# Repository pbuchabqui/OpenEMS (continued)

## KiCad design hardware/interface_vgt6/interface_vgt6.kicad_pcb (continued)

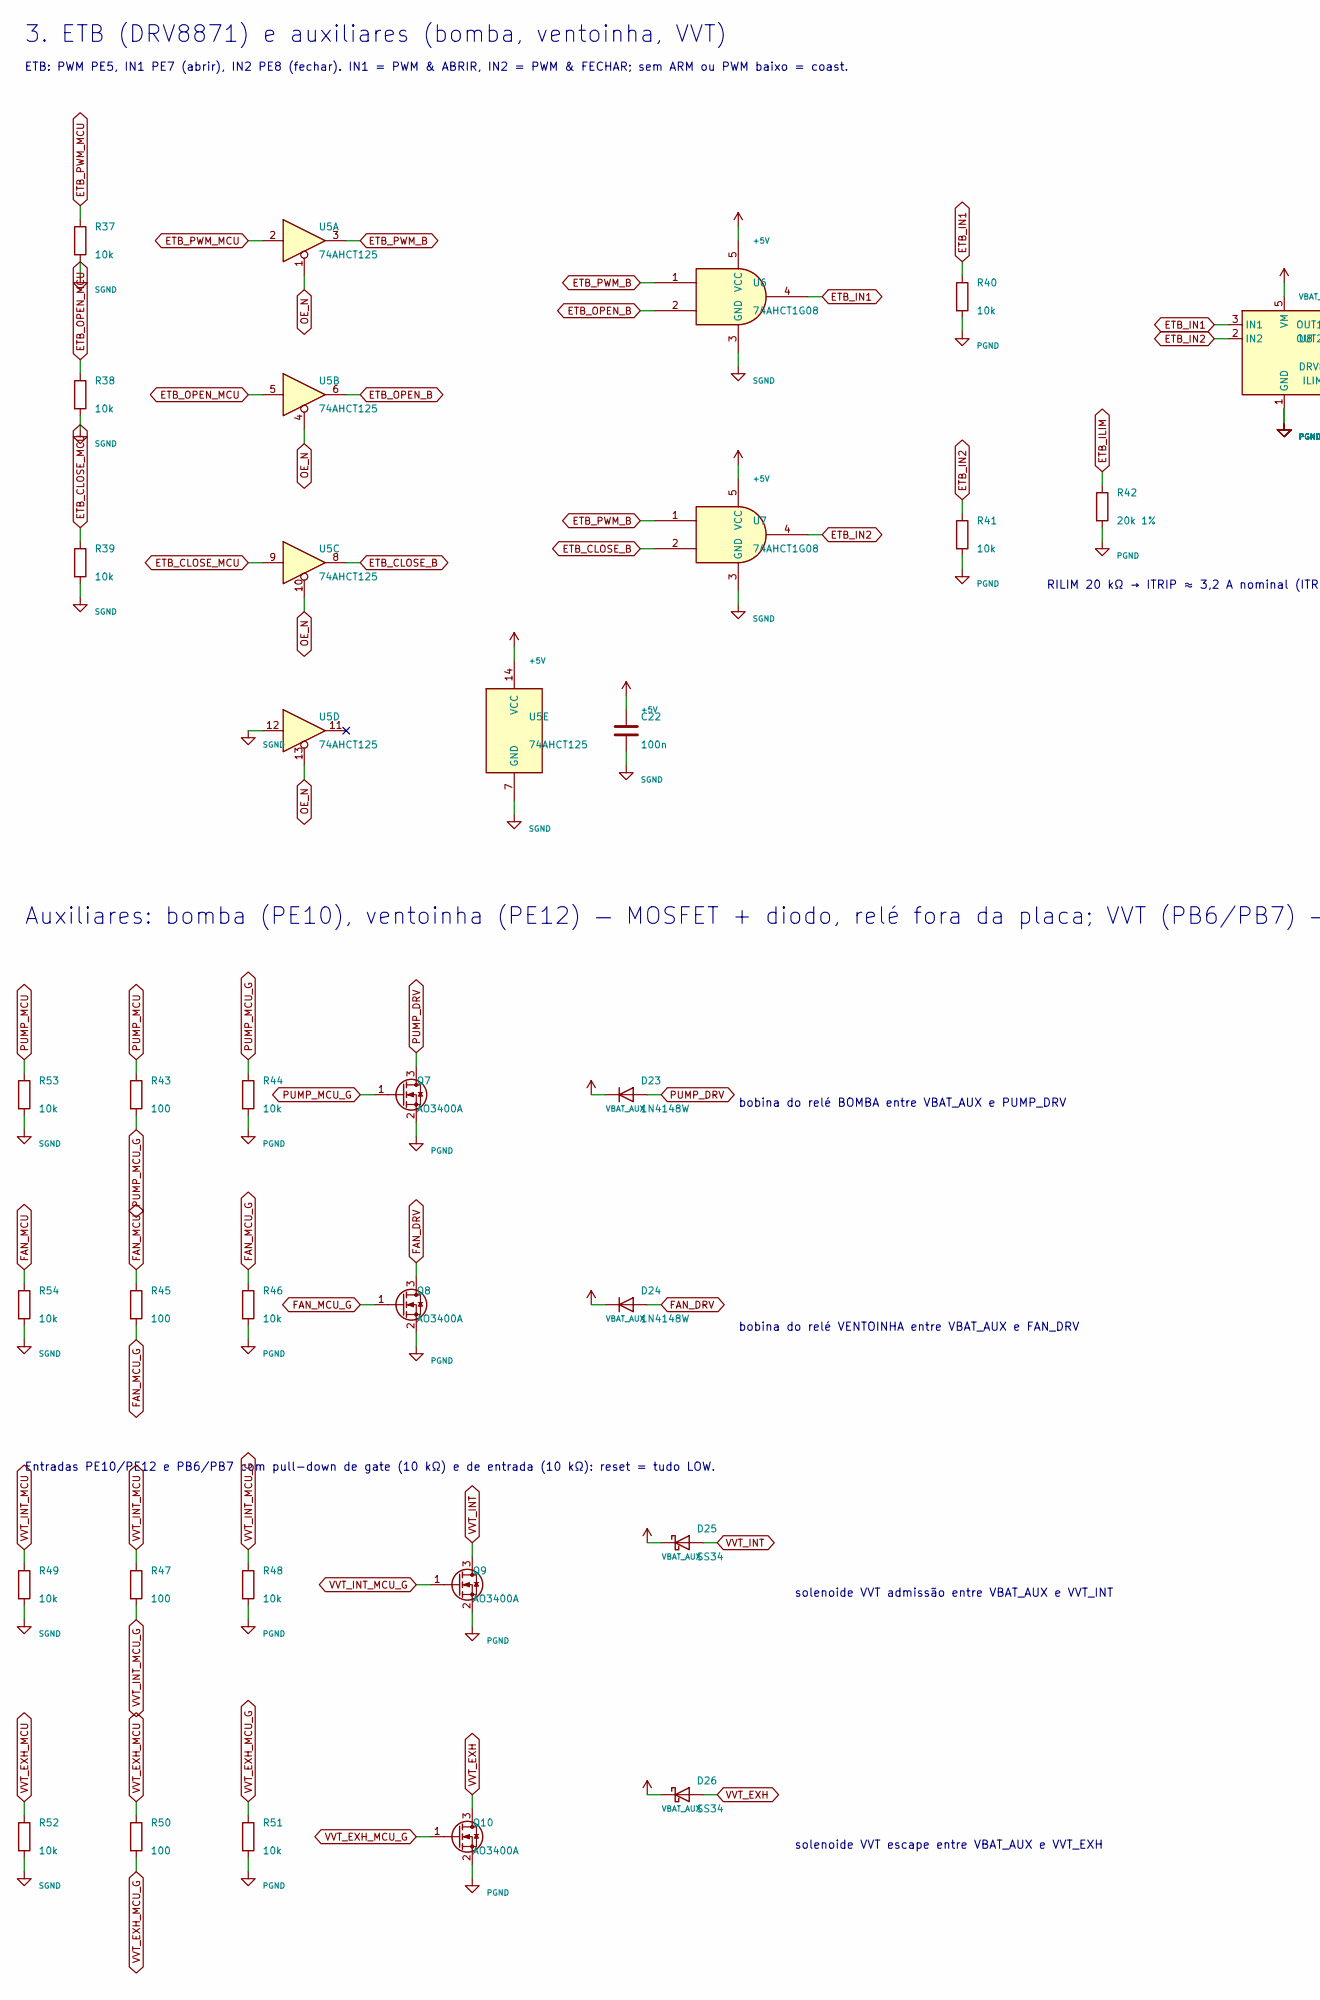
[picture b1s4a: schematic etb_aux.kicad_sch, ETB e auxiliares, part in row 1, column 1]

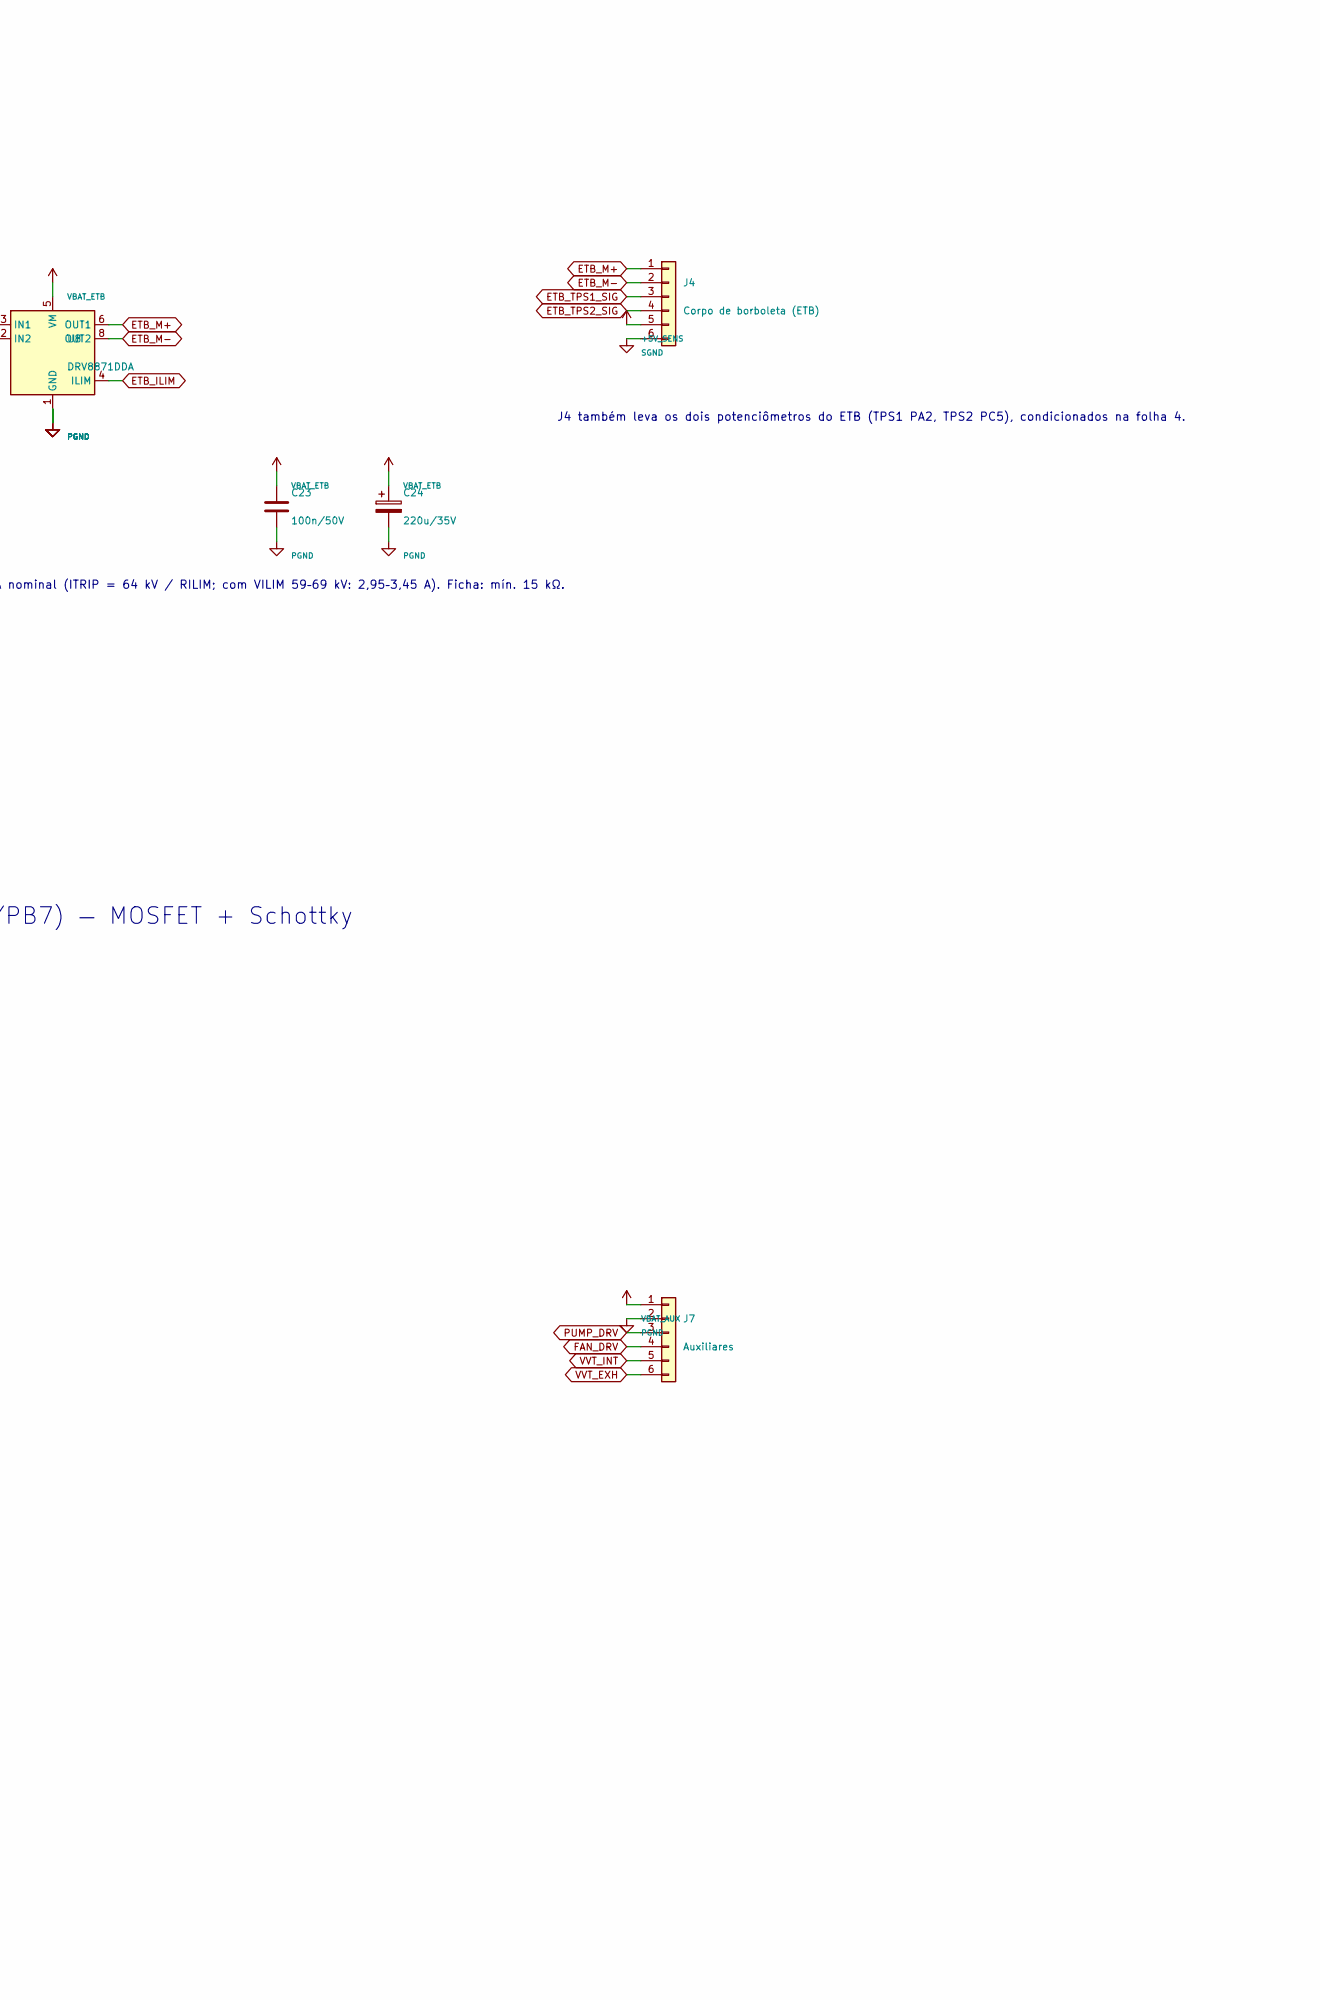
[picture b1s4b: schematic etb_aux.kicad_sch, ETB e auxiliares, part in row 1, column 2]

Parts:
C22: 100n; C_0603_1608Metric
C23: 100n/50V; C_0603_1608Metric
C24: 220u/35V; CP_Elec_8x10
D23, D24: 1N4148W; D_SOD-123
D25, D26: SS34; D_SMA
J4: Corpo de borboleta (ETB); PhoenixContact_MC_1,5_6-G-3.81_1x06_P3.81mm_Horizontal
J7: Auxiliares; PhoenixContact_MSTBA_2,5_6-G-5,08_1x06_P5.08mm_Horizontal
Q7, Q8, Q9, Q10: AO3400A; SOT-23
R37, R38, R39, R40, R41, R44, R46, R48, R49, R51, R52, R53, R54: 10k; R_0603_1608Metric
R42: 20k 1%; R_0603_1608Metric
R43, R45, R47, R50: 100; R_0603_1608Metric
U5: 74AHCT125; TSSOP-14_4.4x5mm_P0.65mm
U6, U7: 74AHCT1G08; SOT-23-5
U8: DRV8871DDA; HSOP-8-1EP_3.9x4.9mm_P1.27mm_EP2.41x3.1mm

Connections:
+5V: C22.1, U5.14 (VCC), U6.5 (VCC), U7.5 (VCC); also elsewhere on the board
+5V_SENS: J4.5; also elsewhere on the board
ETB_CLOSE_B: U5.8, U7.2
ETB_CLOSE_MCU: R39.1, U5.9; also elsewhere on the board
ETB_ILIM: R42.1, U8.4 (ILIM)
ETB_IN1: R40.1, U6.4, U8.3 (IN1)
ETB_IN2: R41.1, U7.4, U8.2 (IN2)
ETB_M+: J4.1, U8.6 (OUT1)
ETB_M-: J4.2, U8.8 (OUT2)
ETB_OPEN_B: U5.6, U6.2
ETB_OPEN_MCU: R38.1, U5.5; also elsewhere on the board
ETB_PWM_B: U5.3, U6.1, U7.1
ETB_PWM_MCU: R37.1, U5.2; also elsewhere on the board
ETB_TPS1_SIG: J4.3; also elsewhere on the board
ETB_TPS2_SIG: J4.4; also elsewhere on the board
FAN_DRV: D24.2 (A), J7.4, Q8.3 (D)
FAN_MCU: R45.1, R54.1; also elsewhere on the board
FAN_MCU_G: Q8.1 (G), R45.2, R46.1
OE_N: U5.1, U5.4, U5.10, U5.13; also elsewhere on the board
PGND: C23.2, C24.2, J7.2, Q7.2 (S), Q8.2 (S), Q9.2 (S), Q10.2 (S), R40.2, R41.2, R42.2, R44.2, R46.2, R48.2, R51.2, U8.1 (GND), U8.7 (GND), U8.9 (GND); also elsewhere on the board
PUMP_DRV: D23.2 (A), J7.3, Q7.3 (D)
PUMP_MCU: R43.1, R53.1; also elsewhere on the board
PUMP_MCU_G: Q7.1 (G), R43.2, R44.1
SGND: C22.2, J4.6, R37.2, R38.2, R39.2, R49.2, R52.2, R53.2, R54.2, U5.7 (GND), U5.12, U6.3 (GND), U7.3 (GND); also elsewhere on the board
VBAT_AUX: D23.1 (K), D24.1 (K), D25.1 (K), D26.1 (K), J7.1; also elsewhere on the board
VBAT_ETB: C23.1, C24.1, U8.5 (VM); also elsewhere on the board
VVT_EXH: D26.2 (A), J7.6, Q10.3 (D)
VVT_EXH_MCU: R50.1, R52.1; also elsewhere on the board
VVT_EXH_MCU_G: Q10.1 (G), R50.2, R51.1
VVT_INT: D25.2 (A), J7.5, Q9.3 (D)
VVT_INT_MCU: R47.1, R49.1; also elsewhere on the board
VVT_INT_MCU_G: Q9.1 (G), R47.2, R48.1

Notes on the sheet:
3. ETB (DRV8871) e auxiliares (bomba, ventoinha, VVT)
ETB: PWM PE5, IN1 PE7 (abrir), IN2 PE8 (fechar). IN1 = PWM & ABRIR, IN2 = PWM & FECHAR; sem ARM ou PWM baixo = coast.
RILIM 20 kΩ → ITRIP ≈ 3,2 A nominal (ITRIP = 64 kV / RILIM; com VILIM 59–69 kV: 2,95–3,45 A). Ficha: mín. 15 kΩ.
J4 também leva os dois potenciômetros do ETB (TPS1 PA2, TPS2 PC5), condicionados na folha 4.
Auxiliares: bomba (PE10), ventoinha (PE12) — MOSFET + diodo, relé fora da placa; VVT (PB6/PB7) — MOSFET + Schottky
bobina do relé BOMBA entre VBAT_AUX e PUMP_DRV
bobina do relé VENTOINHA entre VBAT_AUX e FAN_DRV
solenoide VVT admissão entre VBAT_AUX e VVT_INT
solenoide VVT escape entre VBAT_AUX e VVT_EXH
Entradas PE10/PE12 e PB6/PB7 com pull-down de gate (10 kΩ) e de entrada (10 kΩ): reset = tudo LOW.

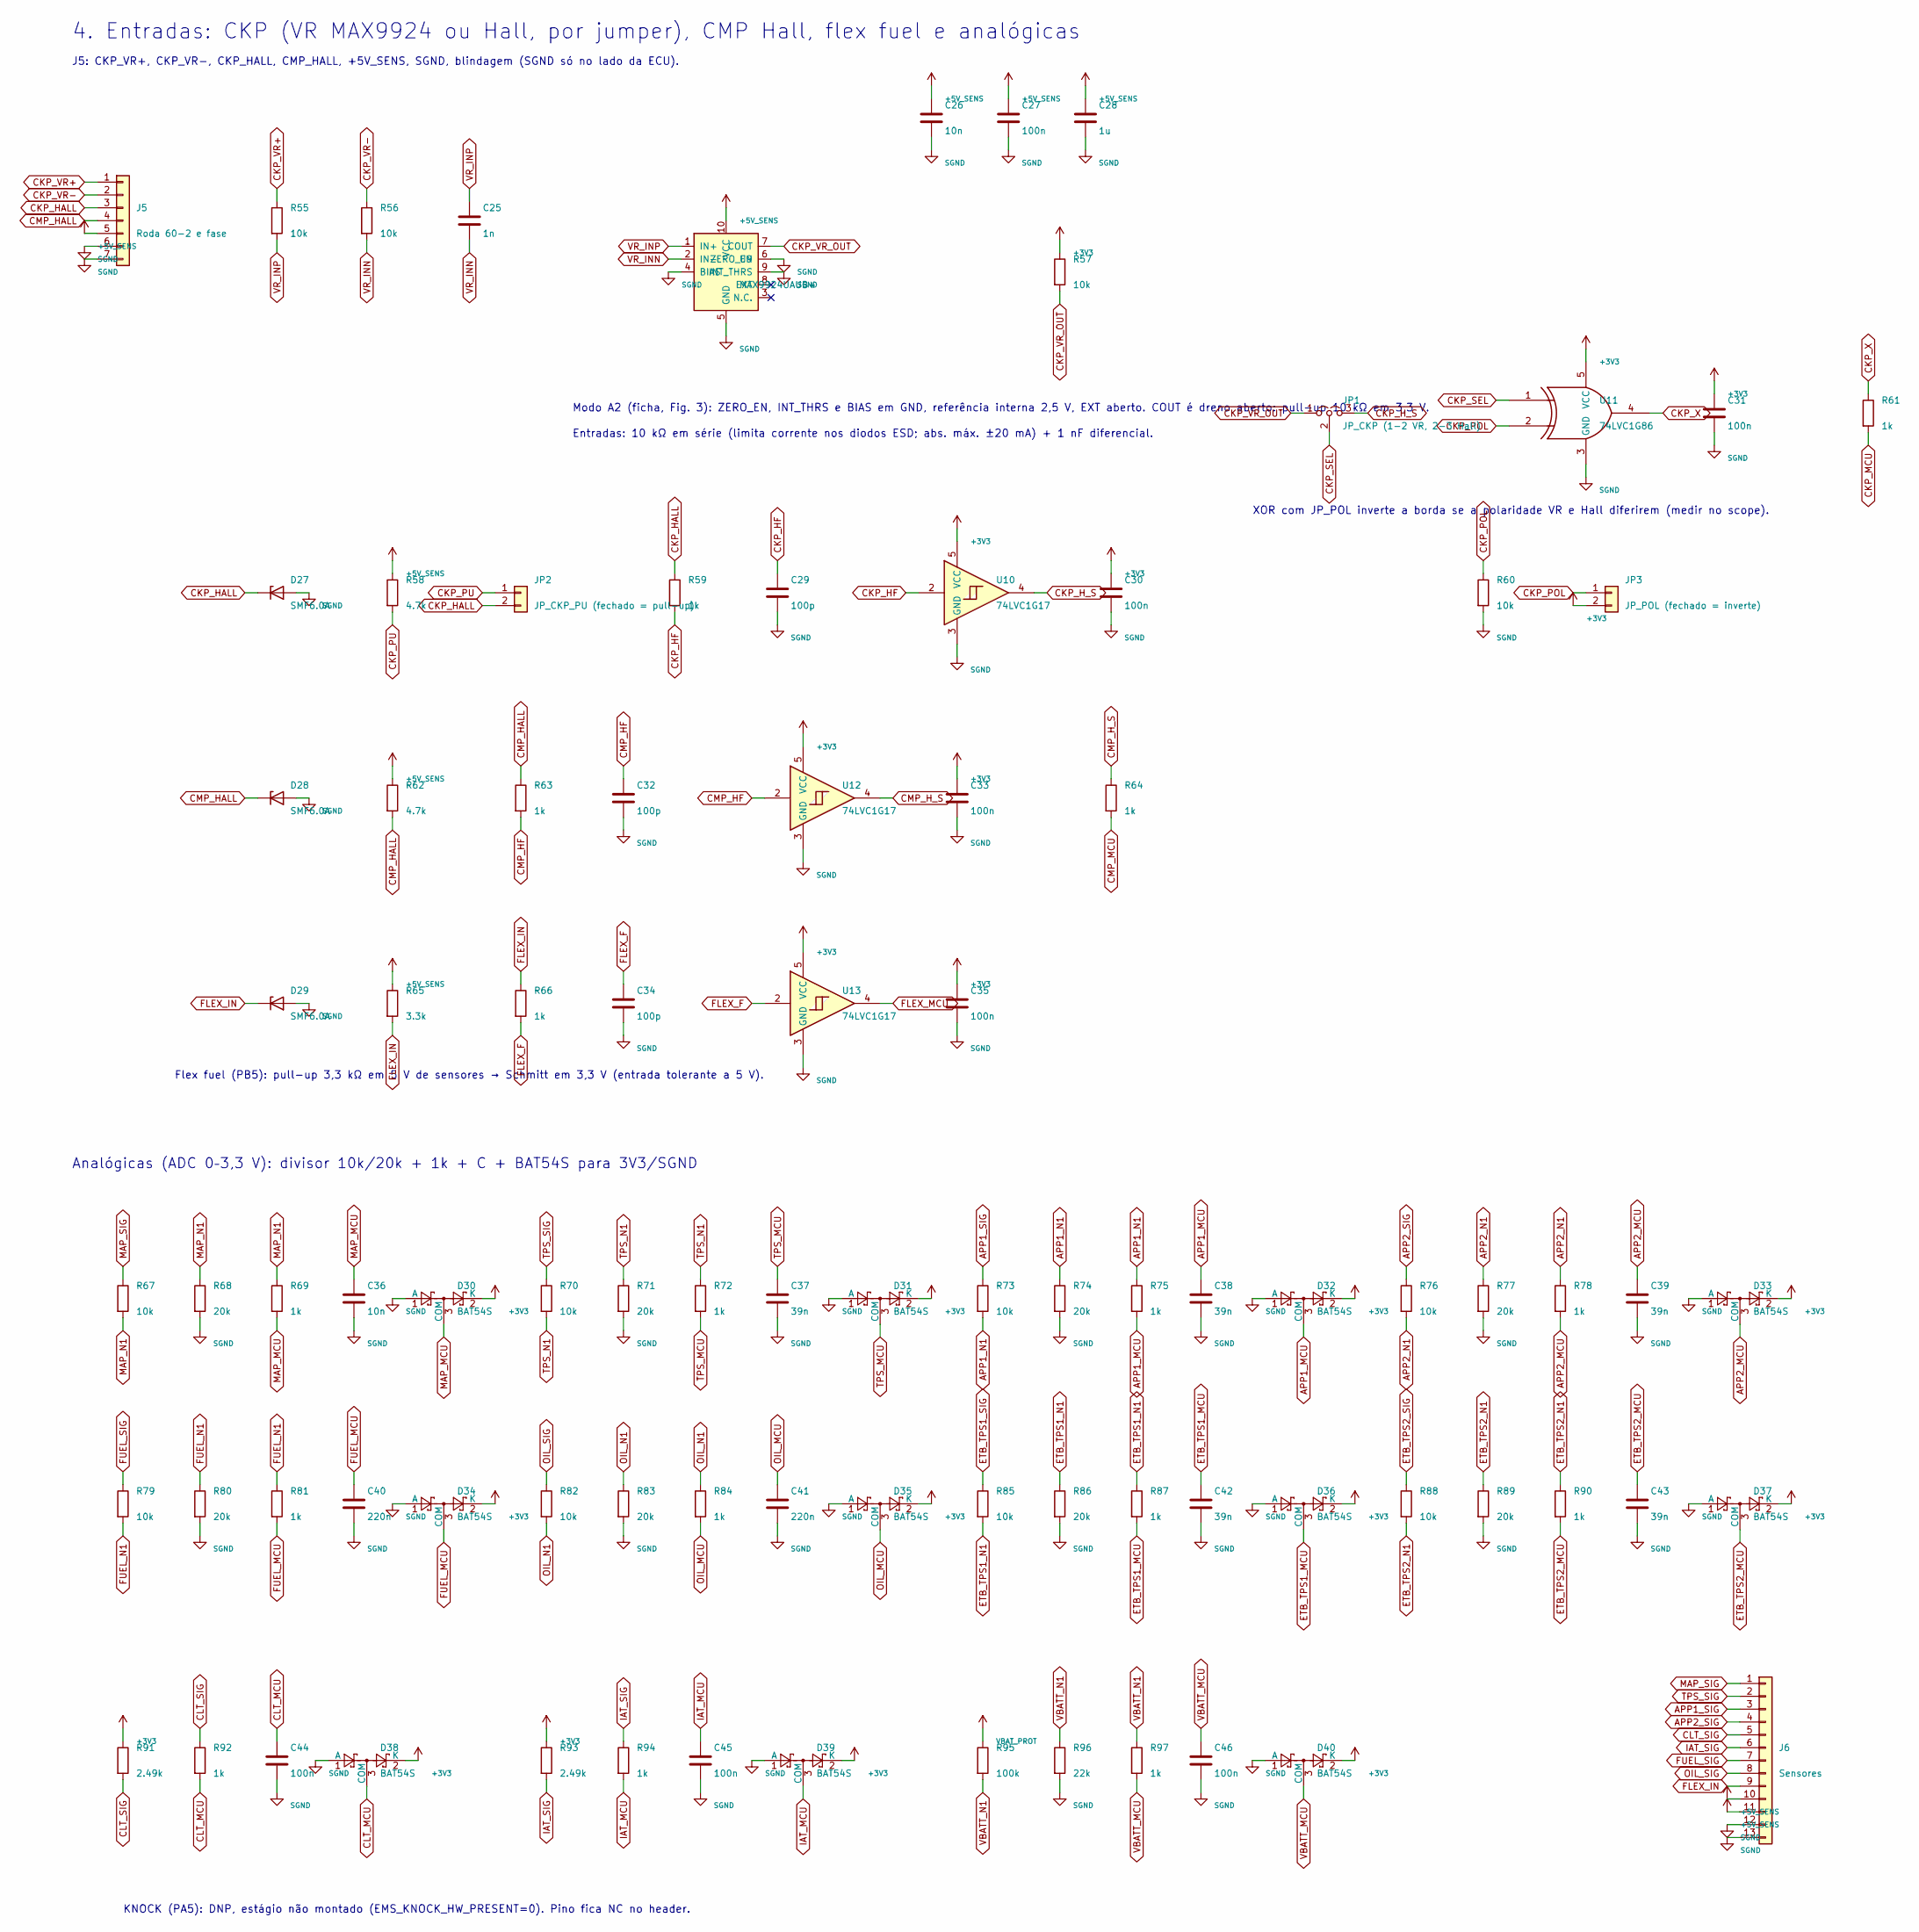
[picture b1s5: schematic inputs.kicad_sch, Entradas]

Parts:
C25: 1n; C_0603_1608Metric
C26, C36: 10n; C_0603_1608Metric
C27, C30, C31, C33, C35, C44, C45, C46: 100n; C_0603_1608Metric
C28: 1u; C_0603_1608Metric
C29, C32, C34: 100p; C_0603_1608Metric
C37, C38, C39, C42, C43: 39n; C_0603_1608Metric
C40, C41: 220n; C_0603_1608Metric
D27, D28, D29: SMF6.0A; D_SOD-123F
D30, D31, D32, D33, D34, D35, D36, D37, D38, D39, D40: BAT54S; SOT-23
J5: Roda 60-2 e fase; PhoenixContact_MC_1,5_7-G-3.81_1x07_P3.81mm_Horizontal
J6: Sensores; PhoenixContact_MC_1,5_13-G-3.81_1x13_P3.81mm_Horizontal
JP1: JP_CKP (1-2 VR, 2-3 Hall); PinHeader_1x03_P2.54mm_Vertical
JP2: JP_CKP_PU (fechado = pull-up); PinHeader_1x02_P2.54mm_Vertical
JP3: JP_POL (fechado = inverte); PinHeader_1x02_P2.54mm_Vertical
R55, R56, R57, R60, R67, R70, R73, R76, R79, R82, R85, R88: 10k; R_0603_1608Metric
R58, R62: 4.7k; R_0603_1608Metric
R59, R61, R63, R64, R66, R69, R72, R75, R78, R81, R84, R87, R90, R92, R94, R97: 1k; R_0603_1608Metric
R65: 3.3k; R_0603_1608Metric
R68, R71, R74, R77, R80, R83, R86, R89: 20k; R_0603_1608Metric
R91, R93: 2.49k; R_0603_1608Metric
R95: 100k; R_0603_1608Metric
R96: 22k; R_0603_1608Metric
U9: MAX9924UAUB+; MSOP-10_3x3mm_P0.5mm
U10, U12, U13: 74LVC1G17; SOT-23-5
U11: 74LVC1G86; SOT-23-5

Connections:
+3V3: C30.1, C31.1, C33.1, C35.1, D30.2 (K), D31.2 (K), D32.2 (K), D33.2 (K), D34.2 (K), D35.2 (K), D36.2 (K), D37.2 (K), D38.2 (K), D39.2 (K), D40.2 (K), JP3.2, R57.1, R91.1, R93.1, U10.5 (VCC), U11.5 (VCC), U12.5 (VCC), U13.5 (VCC); also elsewhere on the board
+5V_SENS: C26.1, C27.1, C28.1, J5.5, J6.10, J6.11, R58.1, R62.1, R65.1, U9.10 (VCC); also elsewhere on the board
APP1_MCU: C38.1, D32.3 (COM), R75.2; also elsewhere on the board
APP1_N1: R73.2, R74.1, R75.1
APP1_SIG: J6.3, R73.1
APP2_MCU: C39.1, D33.3 (COM), R78.2; also elsewhere on the board
APP2_N1: R76.2, R77.1, R78.1
APP2_SIG: J6.4, R76.1
CKP_HALL: D27.1 (K), J5.3, JP2.2, R59.1
CKP_HF: C29.1, R59.2, U10.2
CKP_H_S: JP1.3 (B), U10.4
CKP_MCU: R61.2; also elsewhere on the board
CKP_POL: JP3.1, R60.1, U11.2
CKP_PU: JP2.1, R58.2
CKP_SEL: JP1.2 (C), U11.1
CKP_VR+: J5.1, R55.1
CKP_VR-: J5.2, R56.1
CKP_VR_OUT: JP1.1 (A), R57.2, U9.7 (COUT)
CKP_X: R61.1, U11.4
CLT_MCU: C44.1, D38.3 (COM), R92.2; also elsewhere on the board
CLT_SIG: J6.5, R91.2, R92.1
CMP_HALL: D28.1 (K), J5.4, R62.2, R63.1
CMP_HF: C32.1, R63.2, U12.2
CMP_H_S: R64.1, U12.4
CMP_MCU: R64.2; also elsewhere on the board
ETB_TPS1_MCU: C42.1, D36.3 (COM), R87.2; also elsewhere on the board
ETB_TPS1_N1: R85.2, R86.1, R87.1
ETB_TPS1_SIG: R85.1; also elsewhere on the board
ETB_TPS2_MCU: C43.1, D37.3 (COM), R90.2; also elsewhere on the board
ETB_TPS2_N1: R88.2, R89.1, R90.1
ETB_TPS2_SIG: R88.1; also elsewhere on the board
FLEX_F: C34.1, R66.2, U13.2
FLEX_IN: D29.1 (K), J6.9, R65.2, R66.1
FLEX_MCU: U13.4; also elsewhere on the board
FUEL_MCU: C40.1, D34.3 (COM), R81.2; also elsewhere on the board
FUEL_N1: R79.2, R80.1, R81.1
FUEL_SIG: J6.7, R79.1
IAT_MCU: C45.1, D39.3 (COM), R94.2; also elsewhere on the board
IAT_SIG: J6.6, R93.2, R94.1
MAP_MCU: C36.1, D30.3 (COM), R69.2; also elsewhere on the board
MAP_N1: R67.2, R68.1, R69.1
MAP_SIG: J6.1, R67.1
OIL_MCU: C41.1, D35.3 (COM), R84.2; also elsewhere on the board
OIL_N1: R82.2, R83.1, R84.1
OIL_SIG: J6.8, R82.1
SGND: C26.2, C27.2, C28.2, C29.2, C30.2, C31.2, C32.2, C33.2, C34.2, C35.2, C36.2, C37.2, C38.2, C39.2, C40.2, C41.2, C42.2, C43.2, C44.2, C45.2, C46.2, D27.2 (A), D28.2 (A), D29.2 (A), D30.1 (A), D31.1 (A), D32.1 (A), D33.1 (A), D34.1 (A), D35.1 (A), D36.1 (A), D37.1 (A), D38.1 (A), D39.1 (A), D40.1 (A), J5.6, J5.7, J6.12, J6.13, R60.2, R68.2, R71.2, R74.2, R77.2, R80.2, R83.2, R86.2, R89.2, R96.2, U9.4 (BIAS), U9.5 (GND), U9.6 (ZERO_EN), U9.9 (INT_THRS), U10.3 (GND), U11.3 (GND), U12.3 (GND), U13.3 (GND); also elsewhere on the board
TPS_MCU: C37.1, D31.3 (COM), R72.2; also elsewhere on the board
TPS_N1: R70.2, R71.1, R72.1
TPS_SIG: J6.2, R70.1
VBATT_MCU: C46.1, D40.3 (COM), R97.2; also elsewhere on the board
VBATT_N1: R95.2, R96.1, R97.1
VBAT_PROT: R95.1; also elsewhere on the board
VR_INN: C25.2, R56.2, U9.2 (IN-)
VR_INP: C25.1, R55.2, U9.1 (IN+)

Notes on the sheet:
4. Entradas: CKP (VR MAX9924 ou Hall, por jumper), CMP Hall, flex fuel e analógicas
J5: CKP_VR+, CKP_VR-, CKP_HALL, CMP_HALL, +5V_SENS, SGND, blindagem (SGND só no lado da ECU).
Modo A2 (ficha, Fig. 3): ZERO_EN, INT_THRS e BIAS em GND, referência interna 2,5 V, EXT aberto. COUT é dreno aberto: pull-up 10 kΩ em 3,3 V.
Entradas: 10 kΩ em série (limita corrente nos diodos ESD; abs. máx. ±20 mA) + 1 nF diferencial.
XOR com JP_POL inverte a borda se a polaridade VR e Hall diferirem (medir no scope).
Flex fuel (PB5): pull-up 3,3 kΩ em 5 V de sensores → Schmitt em 3,3 V (entrada tolerante a 5 V).
Analógicas (ADC 0–3,3 V): divisor 10k/20k + 1k + C + BAT54S para 3V3/SGND
KNOCK (PA5): DNP, estágio não montado (EMS_KNOCK_HW_PRESENT=0). Pino fica NC no header.

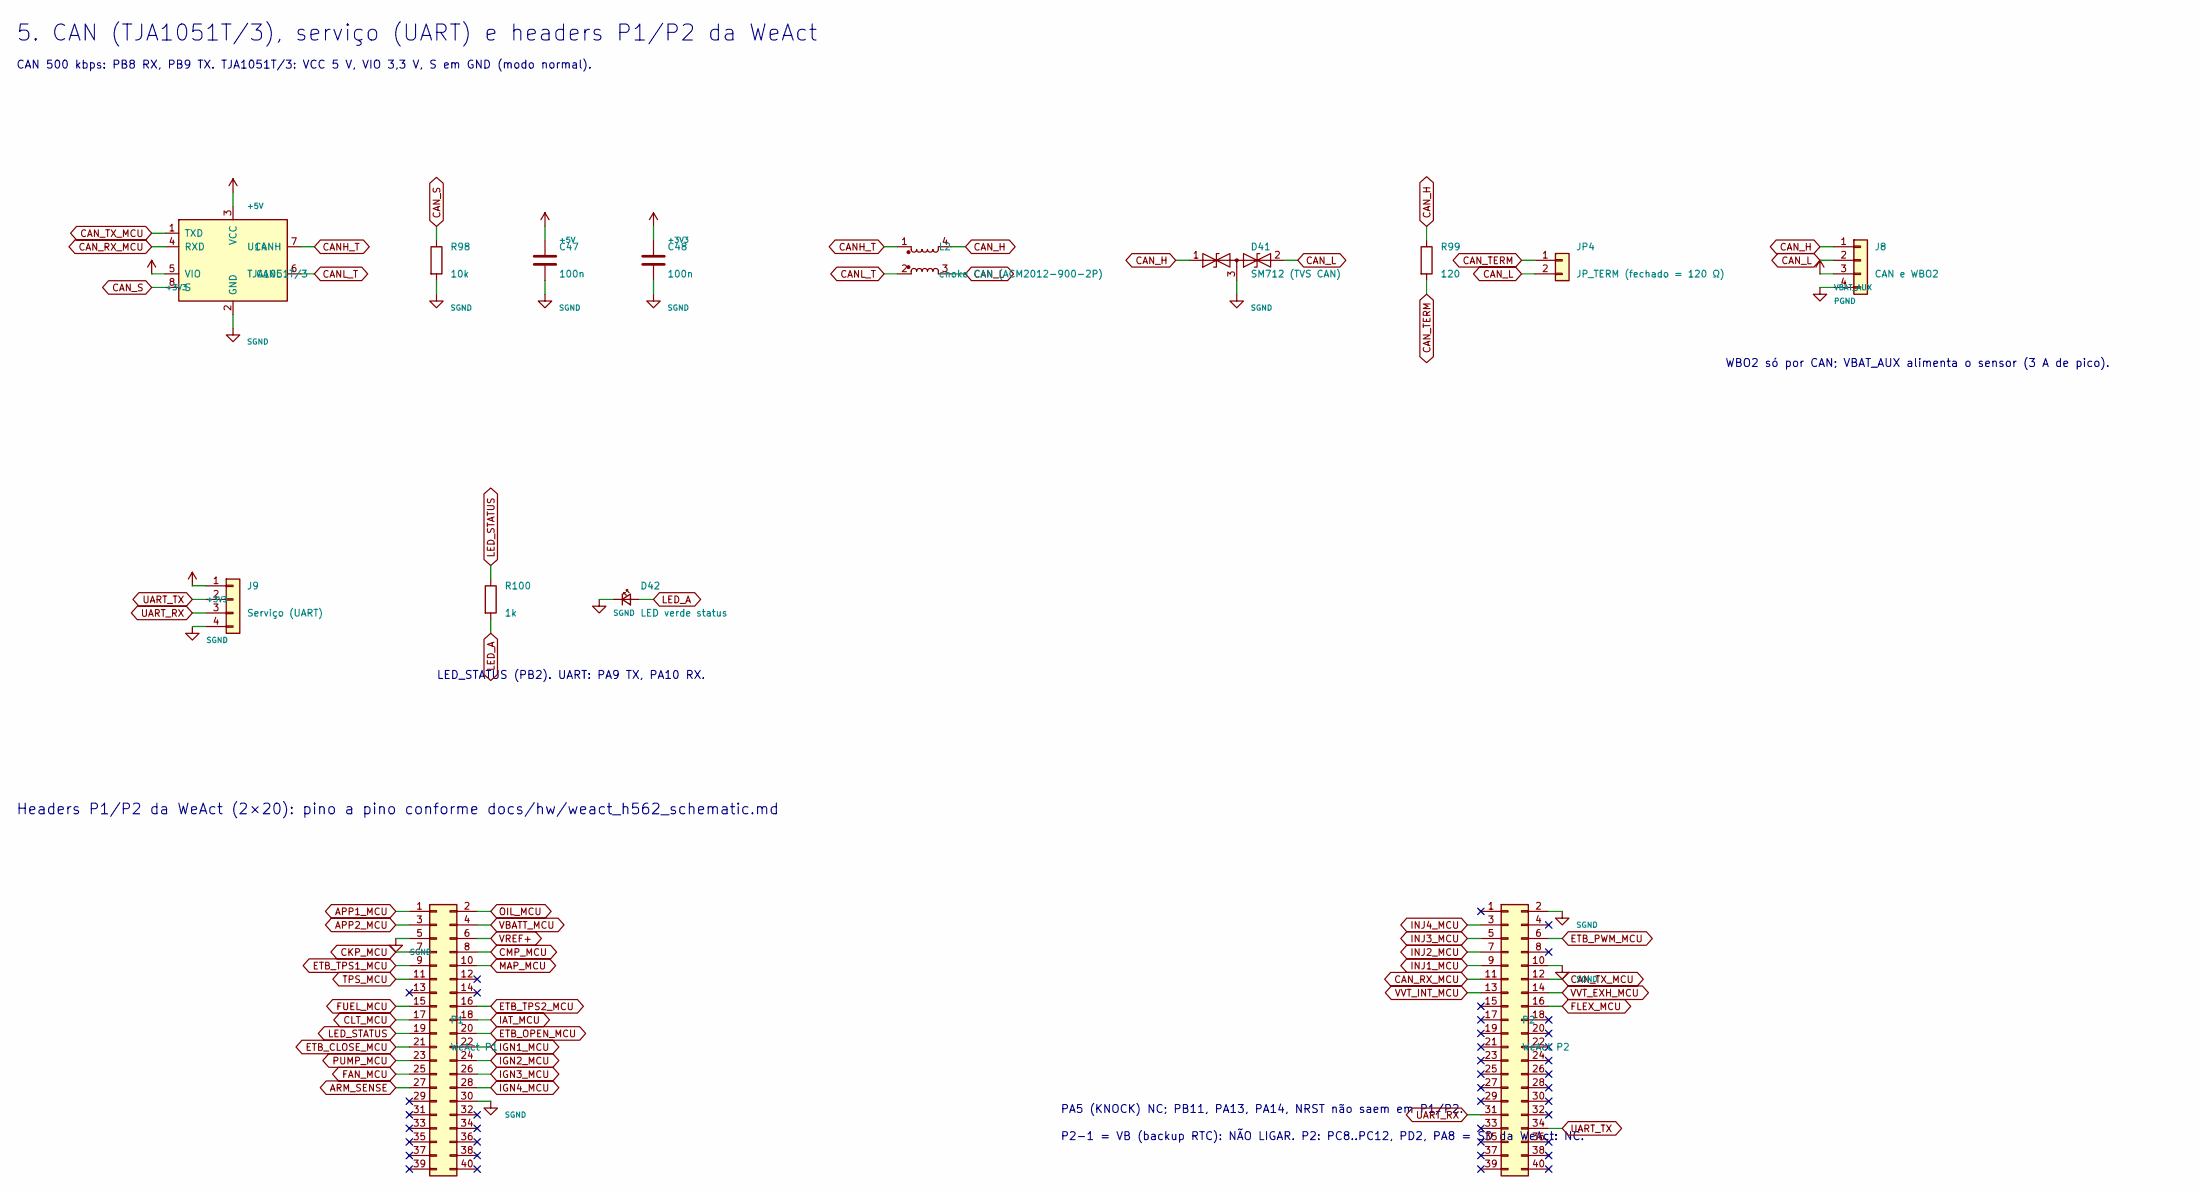
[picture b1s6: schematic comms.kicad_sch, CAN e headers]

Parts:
C47, C48: 100n; C_0603_1608Metric
D41: SM712 (TVS CAN); SOT-23
D42: LED verde status; LED_0603_1608Metric
J8: CAN e WBO2; PhoenixContact_MSTBA_2,5_4-G-5,08_1x04_P5.08mm_Horizontal
J9: Serviço (UART); PinHeader_1x04_P2.54mm_Vertical
JP4: JP_TERM (fechado = 120 Ω); PinHeader_1x02_P2.54mm_Vertical
L2: choke CAN (ACM2012-900-2P); L_CommonModeChoke_Coilank_ACM2012
P1: WeAct P1; PinSocket_2x20_P2.54mm_Vertical
P2: WeAct P2; PinSocket_2x20_P2.54mm_Vertical
R98: 10k; R_0603_1608Metric
R99: 120; R_0603_1608Metric
R100: 1k; R_0603_1608Metric
U14: TJA1051T/3; SOIC-8_3.9x4.9mm_P1.27mm

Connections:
+3V3: C48.1, J9.1, U14.5 (VIO); also elsewhere on the board
+5V: C47.1, U14.3 (VCC); also elsewhere on the board
APP1_MCU: P1.1; also elsewhere on the board
APP2_MCU: P1.3; also elsewhere on the board
ARM_SENSE: P1.27; also elsewhere on the board
CANH_T: L2.1, U14.7 (CANH)
CANL_T: L2.2, U14.6 (CANL)
CAN_H: D41.1 (A1), J8.1, L2.4, R99.1
CAN_L: D41.2 (A2), J8.2, JP4.2, L2.3
CAN_RX_MCU: P2.11, U14.4 (RXD)
CAN_S: R98.1, U14.8 (S)
CAN_TERM: JP4.1, R99.2
CAN_TX_MCU: P2.12, U14.1 (TXD)
CKP_MCU: P1.7; also elsewhere on the board
CLT_MCU: P1.17; also elsewhere on the board
CMP_MCU: P1.8; also elsewhere on the board
ETB_CLOSE_MCU: P1.21; also elsewhere on the board
ETB_OPEN_MCU: P1.20; also elsewhere on the board
ETB_PWM_MCU: P2.6; also elsewhere on the board
ETB_TPS1_MCU: P1.9; also elsewhere on the board
ETB_TPS2_MCU: P1.16; also elsewhere on the board
FAN_MCU: P1.25; also elsewhere on the board
FLEX_MCU: P2.16; also elsewhere on the board
FUEL_MCU: P1.15; also elsewhere on the board
IAT_MCU: P1.18; also elsewhere on the board
IGN1_MCU: P1.22; also elsewhere on the board
IGN2_MCU: P1.24; also elsewhere on the board
IGN3_MCU: P1.26; also elsewhere on the board
IGN4_MCU: P1.28; also elsewhere on the board
INJ1_MCU: P2.9; also elsewhere on the board
INJ2_MCU: P2.7; also elsewhere on the board
INJ3_MCU: P2.5; also elsewhere on the board
INJ4_MCU: P2.3; also elsewhere on the board
LED_A: D42.2 (A), R100.2
LED_STATUS: P1.19, R100.1
MAP_MCU: P1.10; also elsewhere on the board
OIL_MCU: P1.2; also elsewhere on the board
PGND: J8.4; also elsewhere on the board
PUMP_MCU: P1.23; also elsewhere on the board
SGND: C47.2, C48.2, D41.3 (common), D42.1 (K), J9.4, P1.5, P1.30, P2.2, P2.10, R98.2, U14.2 (GND); also elsewhere on the board
TPS_MCU: P1.11; also elsewhere on the board
UART_RX: J9.3, P2.31
UART_TX: J9.2, P2.34
VBATT_MCU: P1.4; also elsewhere on the board
VBAT_AUX: J8.3; also elsewhere on the board
VREF+: P1.6; also elsewhere on the board
VVT_EXH_MCU: P2.14; also elsewhere on the board
VVT_INT_MCU: P2.13; also elsewhere on the board

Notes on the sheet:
5. CAN (TJA1051T/3), serviço (UART) e headers P1/P2 da WeAct
CAN 500 kbps: PB8 RX, PB9 TX. TJA1051T/3: VCC 5 V, VIO 3,3 V, S em GND (modo normal).
WBO2 só por CAN; VBAT_AUX alimenta o sensor (3 A de pico).
LED_STATUS (PB2). UART: PA9 TX, PA10 RX.
Headers P1/P2 da WeAct (2×20): pino a pino conforme docs/hw/weact_h562_schematic.md
PA5 (KNOCK) NC; PB11, PA13, PA14, NRST não saem em P1/P2.
P2-1 = VB (backup RTC): NÃO LIGAR. P2: PC8..PC12, PD2, PA8 = SD da WeAct: NC.

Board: 4 copper layers, 247 parts (0 on the bottom side), 148 nets, no tracks yet.

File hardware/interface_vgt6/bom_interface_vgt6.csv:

Qtd,Referências,Valor,Footprint,Montagem,Risco de estoque,MPN / LCSC (preencher)
3,"C1,C5,C24",220u/35V,CP_Elec_8x10,THT/manual,,
5,"C2,C4,C6,C8,C10",10u/50V,C_1206_3216Metric,SMT,,
1,C3,470u/35V,CP_Elec_10x10.5,THT/manual,,
1,C7,100u/35V,CP_Elec_8x10,THT/manual,,
17,"C9,C15,C17,C18,C20,C21,C22,C27,C30,C31,C33,C35,C44,C45,C46,C47,C48",100n,C_0603_1608Metric,SMT,,
2,"C11,C23",100n/50V,C_0603_1608Metric,SMT,,
2,"C12,C13",22u/10V,C_0805_2012Metric,SMT,,
2,"C14,C16",10u/10V,C_0805_2012Metric,SMT,,
2,"C19,C28",1u,C_0603_1608Metric,SMT,,
1,C25,1n,C_0603_1608Metric,SMT,,
2,"C26,C36",10n,C_0603_1608Metric,SMT,,
3,"C29,C32,C34",100p,C_0603_1608Metric,SMT,,
5,"C37,C38,C39,C42,C43",39n,C_0603_1608Metric,SMT,,
2,"C40,C41",220n,C_0603_1608Metric,SMT,,
2,"D1,D3",SMBJ20A,D_SMB,SMT,,
2,"D2,D4",BZT52C15,D_SOD-123,SMT,NÃO CONSULTADO,
1,D5,LED vermelho (falha 5V sens.),LED_0603_1608Metric,SMT,,
1,D6,LED vermelho ARM,LED_0603_1608Metric,SMT,,
10,"D7,D9,D10,D12,D13,D15,D16,D18,D23,D24",1N4148W,D_SOD-123,SMT,,
4,"D8,D11,D14,D17",SMAJ58A,D_SMA,SMT,NÃO CONSULTADO,
7,"D19,D20,D21,D22,D27,D28,D29",SMF6.0A,D_SOD-123F,SMT,NÃO CONSULTADO (valor de memória),
2,"D25,D26",SS34,D_SMA,SMT,NÃO CONSULTADO,
11,"D30,D31,D32,D33,D34,D35,D36,D37,D38,D39,D40",BAT54S,SOT-23,SMT,,
1,D41,SM712 (TVS CAN),SOT-23,SMT,NÃO CONSULTADO (PESD2CAN esgotado),
1,D42,LED verde status,LED_0603_1608Metric,SMT,,
2,"F1,F4",15A,Fuseholder_Blade_ATO_Littelfuse_Pudenz_2_Pin,THT/manual,,
1,F2,7.5A,Fuseholder_Blade_Mini_Keystone_3568,THT/manual,,
2,"F3,F6",10A,Fuseholder_Blade_Mini_Keystone_3568,THT/manual,,
1,F5,5A,Fuseholder_Blade_Mini_Keystone_3568,THT/manual,,
1,FB1,BLM21 600R/2A,L_0805_2012Metric,SMT,,
4,"H1,H2,H3,H4",M3,MountingHole_3.2mm_M3,THT/manual,,
1,J1A,Entrada A,"PhoenixContact_MSTBA_2,5_4-G-5,08_1x04_P5.08mm_Horizontal",THT/manual,,
1,J1B,Entrada B,"PhoenixContact_MSTBA_2,5_4-G-5,08_1x04_P5.08mm_Horizontal",THT/manual,,
1,J2,Injetores,"PhoenixContact_MSTBA_2,5_5-G-5,08_1x05_P5.08mm_Horizontal",THT/manual,,
1,J3,Ignição,"PhoenixContact_MSTBA_2,5_8-G-5,08_1x08_P5.08mm_Horizontal",THT/manual,,
1,J4,Corpo de borboleta (ETB),"PhoenixContact_MC_1,5_6-G-3.81_1x06_P3.81mm_Horizontal",THT/manual,,
1,J5,Roda 60-2 e fase,"PhoenixContact_MC_1,5_7-G-3.81_1x07_P3.81mm_Horizontal",THT/manual,,
1,J6,Sensores,"PhoenixContact_MC_1,5_13-G-3.81_1x13_P3.81mm_Horizontal",THT/manual,,
1,J7,Auxiliares,"PhoenixContact_MSTBA_2,5_6-G-5,08_1x06_P5.08mm_Horizontal",THT/manual,,
1,J8,CAN e WBO2,"PhoenixContact_MSTBA_2,5_4-G-5,08_1x04_P5.08mm_Horizontal",THT/manual,,
1,J9,Serviço (UART),PinHeader_1x04_P2.54mm_Vertical,THT/manual,,
1,JP1,"JP_CKP (1-2 VR, 2-3 Hall)",PinHeader_1x03_P2.54mm_Vertical,THT/manual,,
1,JP2,JP_CKP_PU (fechado = pull-up),PinHeader_1x02_P2.54mm_Vertical,THT/manual,,
1,JP3,JP_POL (fechado = inverte),PinHeader_1x02_P2.54mm_Vertical,THT/manual,,
1,JP4,JP_TERM (fechado = 120 Ω),PinHeader_1x02_P2.54mm_Vertical,THT/manual,,
1,L1,4.7uH,L_Bourns_SRP7028A_7.3x6.6mm,SMT,,
1,L2,choke CAN (ACM2012-900-2P),L_CommonModeChoke_Coilank_ACM2012,SMT,"NÃO CONSULTADO (o doc de estoque cobriu o ACT45B, não este)",
1,NT1,NetTie PGND-SGND,NetTie-2_SMD_Pad0.5mm,SMT,,
1,P1,WeAct P1,PinSocket_2x20_P2.54mm_Vertical,THT/manual,,
1,P2,WeAct P2,PinSocket_2x20_P2.54mm_Vertical,THT/manual,,
1,P3,"WeAct P3 (VDD33 x2, GND x2)",PinHeader_2x02_P2.54mm_Vertical,THT/manual,,
1,P4,"WeAct P4 (VCC x2, GND x2)",PinHeader_2x02_P2.54mm_Vertical,THT/manual,,
2,"Q1,Q2",AOD4189,TO-252-3_TabPin2,THT/manual,MÉDIO: AOS sem estoque; cópia UMW no LCSC,AOD4189 (LCSC C485685)
4,"Q3,Q4,Q5,Q6",IRLR3110Z,TO-252-3_TabPin2,THT/manual,"BAIXO-MÉDIO: há estoque (DigiKey ≈9,3 mil, Arrow ≈152 mil); 12–52 sem. é prazo de fábrica",IRLR3110ZTRPBF
4,"Q7,Q8,Q9,Q10",AO3400A,SOT-23,SMT,,
45,"R1,R2,R5,R9,R11,R13,R15,R17,R19,R21,R23,R25,R27,R28,R30,R31,R33,R34,R36,R37,R38,R39,R40,R41,R44,R46,R48,R49,R51,R52,R53,R54,R55,R56,R57,R60,R67,R70,R73,R76,R79,R82,R85,R88,R98",10k,R_0603_1608Metric,SMT,,
1,R3,75k 1%,R_0603_1608Metric,SMT,,
19,"R4,R6,R59,R61,R63,R64,R66,R69,R72,R75,R78,R81,R84,R87,R90,R92,R94,R97,R100",1k,R_0603_1608Metric,SMT,,
2,"R7,R95",100k,R_0603_1608Metric,SMT,,
1,R8,150k,R_0603_1608Metric,SMT,,
4,"R10,R14,R18,R22",220,R_0603_1608Metric,SMT,,
4,"R12,R16,R20,R24",47,R_0603_1608Metric,SMT,,
4,"R26,R29,R32,R35",33,R_0603_1608Metric,SMT,,
1,R42,20k 1%,R_0603_1608Metric,SMT,,
4,"R43,R45,R47,R50",100,R_0603_1608Metric,SMT,,
2,"R58,R62",4.7k,R_0603_1608Metric,SMT,,
1,R65,3.3k,R_0603_1608Metric,SMT,,
8,"R68,R71,R74,R77,R80,R83,R86,R89",20k,R_0603_1608Metric,SMT,,
2,"R91,R93",2.49k,R_0603_1608Metric,SMT,,
1,R96,22k,R_0603_1608Metric,SMT,,
1,R99,120,R_0603_1608Metric,SMT,,
1,SW1,ARM (jumper/chave),PinHeader_1x02_P2.54mm_Vertical,THT/manual,,
1,U1,AP63205WU-7,TSOT-23-6,SMT,MÉDIO,
1,U2,TPS2553DBV,SOT-23-6,SMT,MÉDIO: DigiKey esgotado em regiões,TPS2553DBVR (LCSC C55266; não usar -1)
3,"U3,U4,U5",74AHCT125,TSSOP-14_4.4x5mm_P0.65mm,SMT,,
2,"U6,U7",74AHCT1G08,SOT-23-5,SMT,,
1,U8,DRV8871DDA,HSOP-8-1EP_3.9x4.9mm_P1.27mm_EP2.41x3.1mm,SMT,,DRV8871DDAR (LCSC C75864)
1,U9,MAX9924UAUB+,MSOP-10_3x3mm_P0.5mm,SMT,ALTO: fornecedor único,MAX9924UAUB+T (LCSC C5145181; confirmar +/+T)
3,"U10,U12,U13",74LVC1G17,SOT-23-5,SMT,,
1,U11,74LVC1G86,SOT-23-5,SMT,,
1,U14,TJA1051T/3,SOIC-8_3.9x4.9mm_P1.27mm,SMT,,
